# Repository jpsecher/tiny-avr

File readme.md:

# Programming Atmel ATtiny on MacOS

The programmer I use is an AVR-ISP-MK2 from Olimex.

## Programmer

Check that the programmer is connected:

    $ system_profiler SPUSBDataType
      ...
        AVRISP mkII:

          Product ID: 0x2104
          Vendor ID: 0x03eb  (Atmel Corporation)
          Version: 2.00
          Serial Number: 764215213308
          Speed: Up to 12 Mb/sec
          Manufacturer: ATMEL
          Location ID: 0x14700000 / 19
          Current Available (mA): 500
          Extra Operating Current (mA): 0

To communicate with the programmer, install avrdude:

    $ brew install avrdude

Check that communication works:

    $ avrdude -c avrispmkii -p t88

The LED on the programmer should change from orange to green light.

## AVR compiler

Make sure the XCode command-line tools are installed:

    $ xcode-select --install

Install AVR tools:

    $ brew tap osx-cross/avr
    $ brew -v install avr-gcc

It takes a looong time to compile.

## Arduino IDE 1.8

    $ brew cask install arduino

Select the AVR-ISP-MK2 programmer by Tools->Programmer->AVRISPmkII.

Install arduino-tiny package by Arduino->Preferences->Settings->AdditionalBoardsManagerURLs

    http://www.leonardomiliani.com/repository/package_leonardomiliani.com_index.json

Replace the bundled `avrdude` with the Brew version:

  $ cp /usr/local/Cellar/avrdude/6.3_1/bin/avrdude \
       ~/Library/Arduino15/packages/arduino/tools/avrdude/6.0.1-arduino5/bin/avrdude

(or use https://raw.githubusercontent.com/damellis/attiny/ide-1.6.x-boards-manager/package_damellis_attiny_index.json ?)

Load the new boards by Tools->Board->BoardsManager and search for `attiny`.  Click Install, and after that the boards status should read INSTALLED.

## ATtiny2313A / ATtiny4313

Change the speed to 8MHz (see [AVR Fuse Calculator](http://www.engbedded.com/fusecalc/)):

    $ avrdude -p t2313 -U lfuse:w:0xE4:m

Select the board by Tools->Board->ATtiny2313/4313, and the speed Tools->Micro->ATtiny2313@8MHz.

Set the programmer's TARGET jumper to ON and the POWER jumper to 5V so that it can provide power to the ATtiny microcontroller.

Use in-system programmer (ISP/ICSP) output.  Make a cable that can connect the ATtiny (target) to the programmer, cf. the [wiring from the programmer](icsp-cable.png) and how I [split out a 10-wire cable](icsp-wire-split.png), [soldered stiff, coloured wires](cable-heatshrink.jpg) to it, and [finished it up](cable-finished.jpg).

Check that communication works:

    $ avrdude -c avrispmkii -p t2313
    avrdude: AVR device initialized and ready to accept instructions
    Reading | ################################################## | 100% 0.00s
    avrdude: Device signature = 0x1e910a (probably t2313)
    avrdude: safemode: Fuses OK (E:FF, H:DF, L:64)

Make it blink with Aduino IDE:

    #define PIN_16 13
    void setup() {
      pinMode(PIN_16, OUTPUT);
    }
    void loop() {
      digitalWrite(PIN_16, HIGH);
      delay(500);
      digitalWrite(PIN_16, LOW);
      delay(500);
    }

Change to pure C++: https://electronut.in/getting-started-with-attiny85-avr-programming/

Use with external crystal oscillator (>=8MHz, maximum upstart time):

    $ avrdude -p t2313 -U lfuse:w:0xFF:m -U hfuse:w:0xDF:m

I use a 12.288 MHz crystal because I have a bunch of them.

The [datasheet](http://ww1.microchip.com/downloads/en/devicedoc/8246s.pdf).  More at [Microchip](https://www.microchip.com/wwwproducts/en/ATtiny2313).

## ATtiny 13A

The [datasheet](http://ww1.microchip.com/downloads/en/DeviceDoc/doc8126.pdf).

## ATtiny10

The [datasheet](http://ww1.microchip.com/downloads/en/DeviceDoc/atmel-8127-avr-8-bit-microcontroller-attiny4-attiny5-attiny9-attiny10_datasheet.pdf).

### Setup for 12V programming

Connect the AVR-ISP-MK2 directly to the ATtiny10 via TPI, see [picture](?).  Use [AVR Fuse Calculator](http://www.engbedded.com/fusecalc/) and https://www.avrfreaks.net/forum/fuse-rstdisbl-attiny10 to see how to set RSTDISBL:

    $ avrdude -c avrispmkii -p t10 -U fuse:w:0xfe:m

After that it is only possible to program with 12V on reset pin.

### Programming using 12V programmer board

See `tiny-12V-programmer` directory for schematic, PCB, etc. 

With the ATtiny10 fused to RSTDISBL and placed in the 12V programmer board, run a connectivity test:

    $ avrdude -c avrispmkii -p t10 

## MIDI receive

- Install MIDI Library from Forty Seven Effects in Arduino IDE.
- https://www.instructables.com/id/Send-and-Receive-MIDI-with-Arduino/

## Notes

To get rid of an old installation:

    $ brew cask uninstall arduino
    $ rm -rf ~/Library/Arduino15

Protocols:

- USI SPI: https://www.microchip.com/wwwAppNotes/AppNotes.aspx?appnote=en591657
- UART: https://www.microchip.com/wwwAppNotes/AppNotes.aspx?appnote=en591208

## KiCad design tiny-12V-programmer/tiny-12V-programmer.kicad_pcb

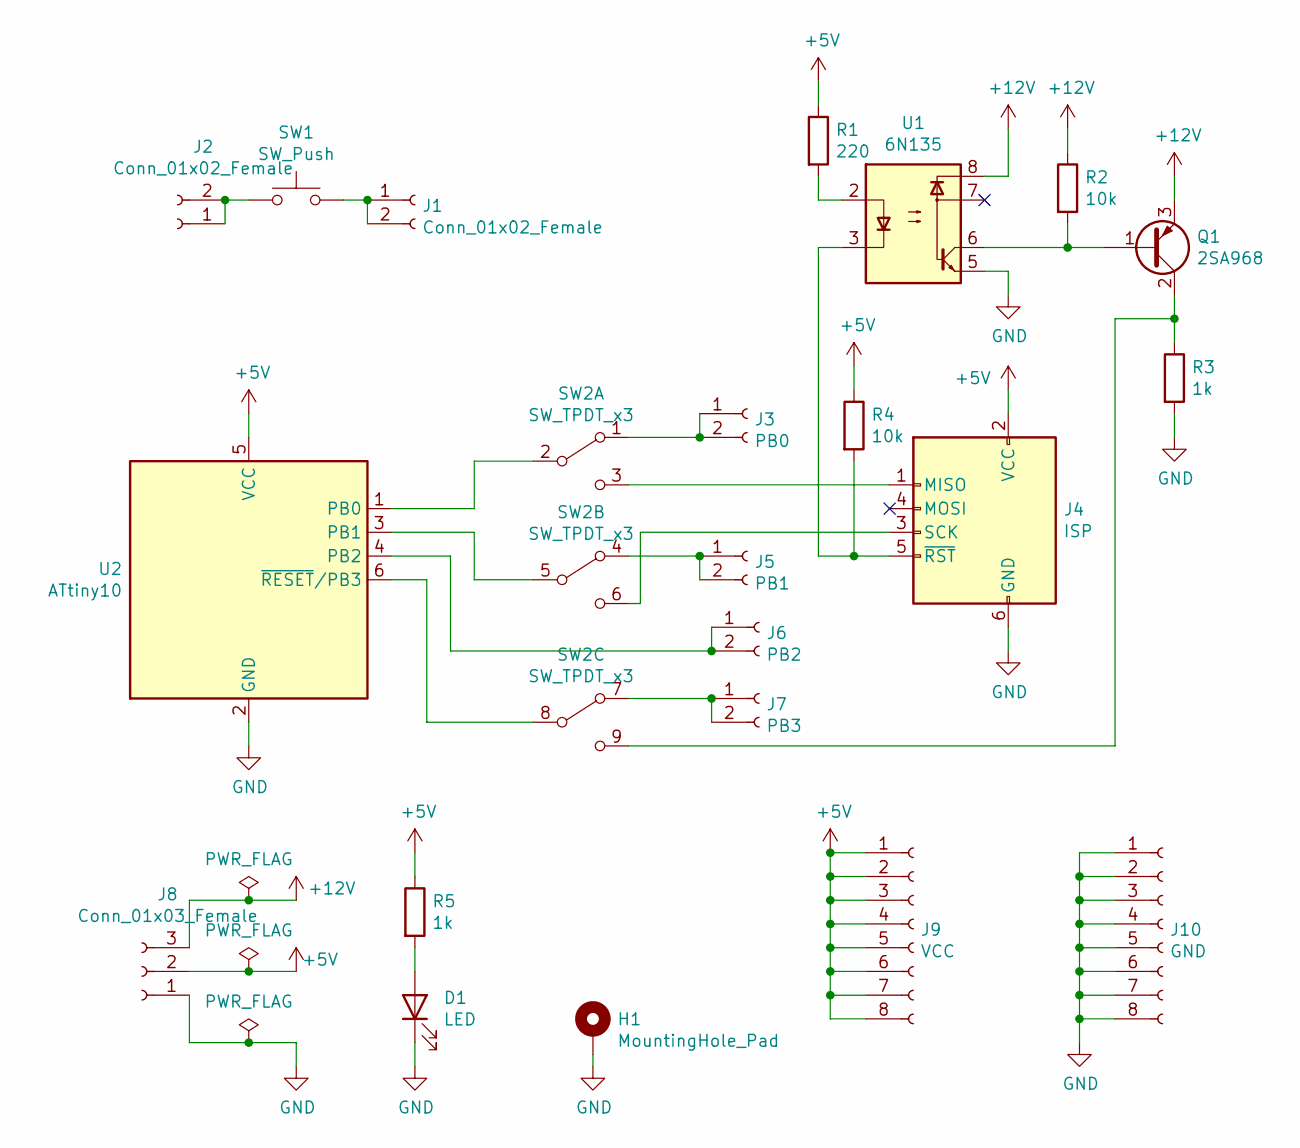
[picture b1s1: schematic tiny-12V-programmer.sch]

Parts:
D1: LED; D_SOT-23_ANK
H1: MountingHole_Pad; MountingHole_3.2mm_M3_Pad
J1, J2: Conn_01x02_Female; PinSocket_1x02_P2.54mm_Vertical
J3: PB0; PinSocket_1x02_P2.54mm_Vertical
J4: ISP; IDC-Header_2x03_P2.54mm_Vertical
J5: PB1; PinSocket_1x02_P2.54mm_Vertical
J6: PB2; PinSocket_1x02_P2.54mm_Vertical
J7: PB3; PinSocket_1x02_P2.54mm_Vertical
J8: Conn_01x03_Female; PinHeader_1x03_P2.54mm_Vertical
J9: VCC; PinSocket_1x08_P2.54mm_Vertical
J10: GND; PinSocket_1x08_P2.54mm_Vertical
Q1: 2SA968; TO-220-3_Horizontal_TabDown
R1: 220; R_0805_2012Metric_Pad1.20x1.40mm_HandSolder
R2, R4: 10k; R_0805_2012Metric_Pad1.20x1.40mm_HandSolder
R3: 1k; R_Axial_DIN0207_L6.3mm_D2.5mm_P10.16mm_Horizontal
R5: 1k; R_1206_3216Metric_Pad1.30x1.75mm_HandSolder
SW1: SW_Push; SW_Push_1P1T_NO_6x6mm_H9.5mm
SW2: SW_TPDT_x3; SW_TPDT
U1: 6N135; DIP-8_W7.62mm
U2: ATtiny10; pin-socket-02x03

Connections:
+5V: J4.2 (VCC), J8.2, J9.1, J9.2, J9.3, J9.4, J9.5, J9.6, J9.7, J9.8, R1.1, R4.1, R5.1, U2.5 (VCC)
+12V: J8.3, Q1.3 (E), R2.1, U1.8
GND: D1.1 (K), H1.1, J4.6 (GND), J8.1, J10.1, J10.2, J10.3, J10.4, J10.5, J10.6, J10.7, J10.8, R3.2, U1.5, U2.2 (GND)
unnamed: D1.2 (A), R5.2
unnamed: J1.1, J1.2, SW1.2
unnamed: J2.1, J2.2, SW1.1
unnamed: J3.1, J3.2, SW2.1 (A)
unnamed: J4.1 (MISO), SW2.3 (C)
unnamed: J4.3 (SCK), SW2.6 (C)
unnamed: J4.5 (~RST), R4.2, U1.3
unnamed: J5.1, J5.2, SW2.4 (A)
unnamed: J6.1, J6.2, U2.4 (PB2)
unnamed: J7.1, J7.2, SW2.7 (A)
unnamed: Q1.1 (B), R2.2, U1.6
unnamed: Q1.2 (C), R3.1, SW2.9 (C)
unnamed: R1.2, U1.2
unnamed: SW2.2 (B), U2.1 (PB0)
unnamed: SW2.5 (B), U2.3 (PB1)
unnamed: SW2.8 (B), U2.6 (~RESET~/PB3)

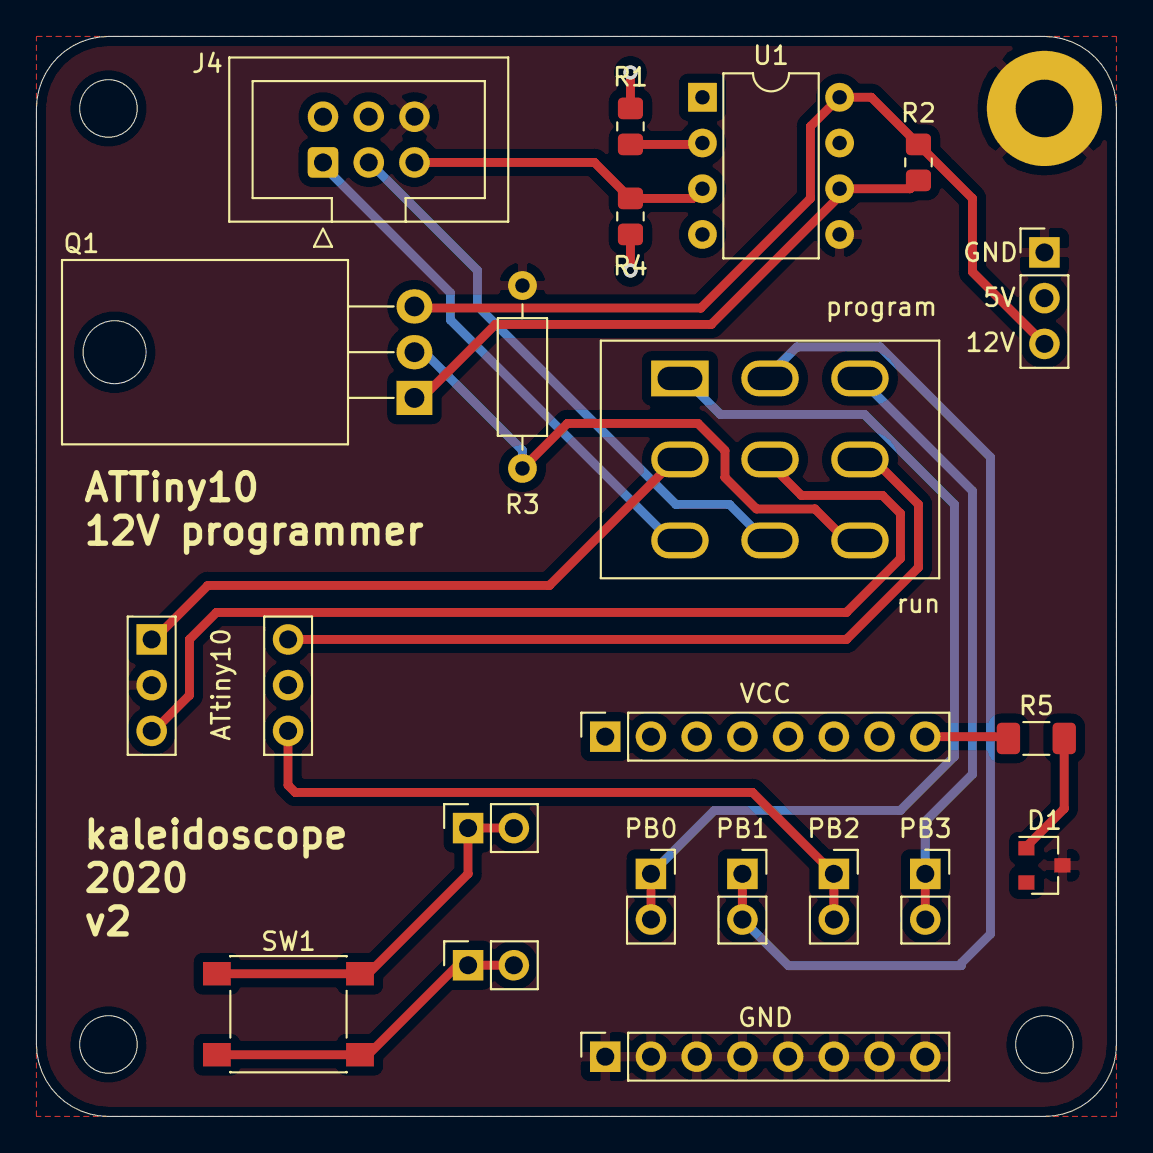
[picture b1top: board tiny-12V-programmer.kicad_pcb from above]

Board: 2 copper layers, 60.0 x 60.0 mm, 22 parts (0 on the bottom side), 19 nets.

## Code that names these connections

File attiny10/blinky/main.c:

/*
  Connections:

  PB0 --- +LED- --- GND

  PB1 --- +LED- --- GND

  PB2 --- +LED- --- GND

  PB3 --- +LED- --- GND
*/

#define F_CPU 1000000  // 1MHz because divided by 8 by default

#include <avr/io.h>
#include <util/delay.h>

#define INLINE static inline

INLINE void all_pins_as_output (void);
INLINE void pin_on (uint8_t pin);
INLINE void pin_off (uint8_t pin);

int main () {
  all_pins_as_output();
  while (1) {
    pin_on(PB0);
    _delay_ms(100);
    pin_off(PB0);
    pin_on(PB1);
    _delay_ms(100);
    pin_off(PB1);
    pin_on(PB2);
    _delay_ms(100);
    pin_off(PB2);
    pin_on(PB3);
    _delay_ms(100);
    pin_off(PB3);
    _delay_ms(500);
  }
  return 0;
}

void all_pins_as_output (void) {
  DDRB = _BV(PB0) | _BV(PB1) | _BV(PB2) | _BV(PB3);
}

void pin_on (uint8_t pin) {
  PORTB |= _BV(pin);
}

void pin_off (uint8_t pin) {
  PORTB &= ~_BV(pin);
}

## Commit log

2019-01-18 License.
2019-01-18 WIP: programmer & macos setup.
2019-01-18 Cable.
2019-01-20 Overwrite avrdude.
2019-01-21 Set ATTiny2313A to 8MHz.
2019-01-21 Blinky without Arduino.
2019-01-21 Inline functions.
2019-01-21 Use Bit Value from library.
2019-01-21 Make blinky work with ATTiny13A also.
2019-01-22 Link to SPI & UART implementations.
2019-01-22 Cleanup makefile.
2019-01-27 External crystal.
2019-02-19 WIP: I2C
2019-02-20 Communitcation with MCP4725 works.
2019-02-23 rearrange.
2019-02-23 small functions.
2019-02-23 Prepare bits before transfer.
2019-02-23 toggle func.
2019-02-23 Timing.
2019-02-23 Release == pullup.
2019-02-23 Error code blink
2019-02-23 Report errors.
2019-02-23 missing stop.
2019-02-23 braces.
2019-02-23 write_byte.
2019-02-23 usi_read_ack
2019-02-23 usi_wait_for_scl_release
2019-02-23 usi_send_until_transfer_complete
2019-02-23 fail bus noise.
2019-02-23 INLINE.
2019-02-23 Refactoring.
2019-02-23 Always inline.
2019-02-23 lower LED intensity.
2019-02-25 DAC step ramp with every MIDI recevied.
2019-02-25 DAC responds to MIDI click messages.
2019-02-26 macros.
2019-06-22 Precise timing via Timer/Counter IRQ.
2019-06-23 Stop interupts while reading time.
2019-06-23 Button input via IRQ.
2020-03-31 Notes.
2020-12-05 ATTiny 10 12V programmer
2020-12-17 Adjust TPDT switch footprint to fit
2021-07-31 Corrections to v1
2021-08-01 Blinky for attiny10
2021-08-01 Clock speed
2021-08-01 Input
2021-08-01 CTC mode PWM
2021-08-02 ADC controlled buzzer
2021-08-05 ATtiny88 blinky
2021-08-07 ATtiny88 dual LED
2021-08-07 WIP: status blinking
2021-08-07 Data indexing
2021-08-07 Conform access to status
2021-08-07 Input with pull up
2021-08-07 WIP: interrupt on button
2021-08-08 Not working: function pointers
2021-08-08 Dispatch processing directly
2021-08-08 Handlers by function pointers
2021-08-08 WIP: encoder
2021-08-08 Encoder
2021-08-09 Switched A & B
2021-08-09 Simplify error example
2021-08-11 Moved Encoder & LED
2021-08-16 LCD hello world
2021-08-16 Blink control
2021-08-16 Solid cursor
2021-08-16 custom char
2021-08-16 Danish
2021-08-30 Update Blink Error to new pinout
2021-08-30 Prepare for DAC i2C
2021-08-30 Spelling
2021-09-04 TWI init
2021-09-05 I2C master -> DAC working
2021-09-06 Refactor
2021-09-06 Clean up
2021-09-17 WIP: internal ADC
2021-09-18 ADC working
2021-09-18 Cleanup
2021-09-18 Disable digital
2021-11-21 use ICSP10
2021-11-21 More stable encoder
2022-02-02 Use MIT-0 license
2022-02-02 MIT license
